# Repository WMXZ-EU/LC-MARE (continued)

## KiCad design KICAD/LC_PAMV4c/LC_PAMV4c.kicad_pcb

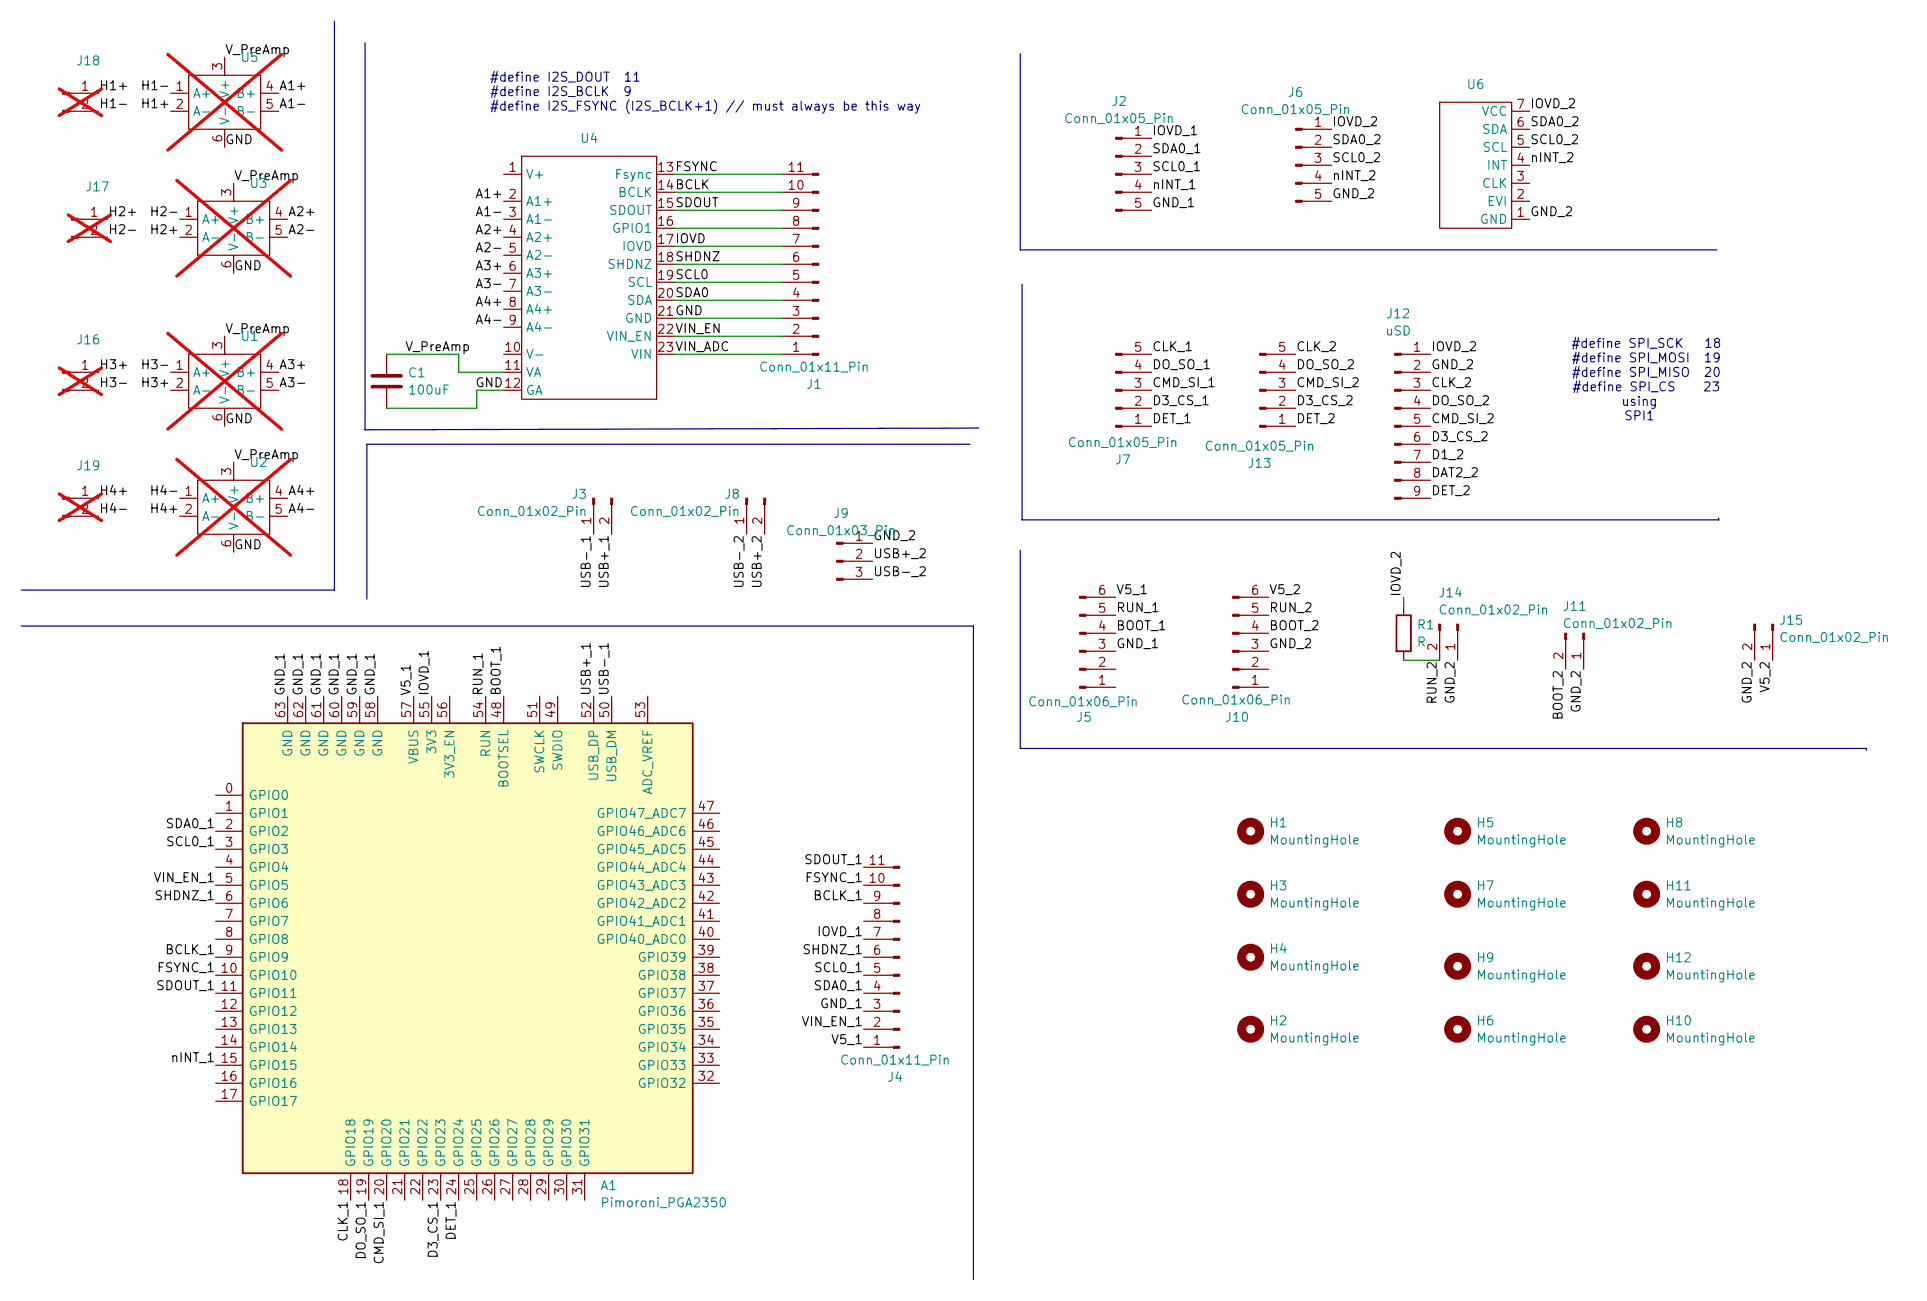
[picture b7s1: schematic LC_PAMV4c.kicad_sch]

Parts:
A1: Pimoroni_PGA2350; pimoroni_pga2350
C1: 100uF; CP_Radial_D4.0mm_P2.00mm
H1, H2, H3, H4, H5, H6, H7, H8, H9, H10, H11, H12: MountingHole; MountingHole_4.3mm_M4
J1, J4: Conn_01x11_Pin; PinHeader_1x11_P2.54mm_Vertical
J2, J6, J7, J13: Conn_01x05_Pin; PinHeader_1x05_P2.54mm_Vertical
J3, J8, J11, J14, J15: Conn_01x02_Pin; PinHeader_1x02_P2.54mm_Vertical
J5, J10: Conn_01x06_Pin; PinHeader_1x06_P2.54mm_Vertical
J9: Conn_01x03_Pin; PinHeader_1x03_P2.54mm_Vertical
J12: uSD
J16, J17, J18, J19: Conn_01x02_Male; Molex_PicoBlade_53048-0210_1x02_P1.25mm_Horizontal; not fitted
R1: R; R_Axial_DIN0204_L3.6mm_D1.6mm_P5.08mm_Horizontal
U1, U2, U3, U5: preAmp2; not fitted
U4: ADC_V2
U6: rtc2

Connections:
/A1+: U4.2 (A1+), U5.4 (B+)
/A1-: U4.3 (A1-), U5.5 (B-)
/A2+: U3.4 (B+), U4.4 (A2+)
/A2-: U3.5 (B-), U4.5 (A2-)
/A3+: U1.4 (B+), U4.6 (A3+)
/A3-: U1.5 (B-), U4.7 (A3-)
/A4+: U2.4 (B+), U4.8 (A4+)
/A4-: U2.5 (B-), U4.9 (A4-)
/BCLK: J1.10, U4.14 (BCLK)
/BCLK_1: A1.9 (GPIO9), J4.9
/BOOT_1: A1.48 (BOOTSEL), J5.4
/BOOT_2: J10.4, J11.2
/CLK_1: A1.18 (GPIO18), J7.5
/CLK_2: J12.3, J13.5
/CMD_SI_1: A1.20 (GPIO20), J7.3
/CMD_SI_2: J12.5, J13.3
/D1_2: J12.7
/D3_CS_1: A1.23 (GPIO23), J7.2
/D3_CS_2: J12.6, J13.2
/DAT2_2: J12.8
/DET_1: A1.24 (GPIO24), J7.1
/DET_2: J12.9, J13.1
/DO_SO_1: A1.19 (GPIO19), J7.4
/DO_SO_2: J12.4, J13.4
/FSYNC: J1.11, U4.13 (Fsync)
/FSYNC_1: A1.10 (GPIO10), J4.10
/GND: C1.2, J1.3, U1.6 (V-), U2.6 (V-), U3.6 (V-), U4.12 (GA), U4.21 (GND), U5.6 (V-)
/GND_1: A1.58 (GND), A1.59 (GND), A1.60 (GND), A1.61 (GND), A1.62 (GND), A1.63 (GND), J2.5, J4.3, J5.3
/GND_2: J6.5, J9.1, J10.3, J11.1, J12.2, J14.1, J15.2, U6.1 (GND)
/H1+: J18.1, U5.2 (A-)
/H1-: J18.2, U5.1 (A+)
/H2+: J17.1, U3.2 (A-)
/H2-: J17.2, U3.1 (A+)
/H3+: J16.1, U1.2 (A-)
/H3-: J16.2, U1.1 (A+)
/H4+: J19.1, U2.2 (A-)
/H4-: J19.2, U2.1 (A+)
/IOVD: J1.7, U4.17 (IOVD)
/IOVD_1: A1.55 (3V3), J2.1, J4.7
/IOVD_2: J6.1, J12.1, R1.1, U6.7 (VCC)
/RUN_1: A1.54 (RUN), J5.5
/RUN_2: J10.5, J14.2, R1.2
/SCL0: J1.5, U4.19 (SCL)
/SCL0_1: A1.3 (GPIO3), J2.3, J4.5
/SCL0_2: J6.3, U6.5 (SCL)
/SDA0: J1.4, U4.20 (SDA)
/SDA0_1: A1.2 (GPIO2), J2.2, J4.4
/SDA0_2: J6.2, U6.6 (SDA)
/SDOUT: J1.9, U4.15 (SDOUT)
/SDOUT_1: A1.11 (GPIO11), J4.11
/SHDNZ: J1.6, U4.18 (SHDNZ)
/SHDNZ_1: A1.6 (GPIO6), J4.6
/USB+_1: A1.52 (USB_DP), J3.2
/USB+_2: J8.2, J9.2
/USB-_1: A1.50 (USB_DM), J3.1
/USB-_2: J8.1, J9.3
/V5_1: A1.57 (VBUS), J4.1, J5.6
/V5_2: J10.6, J15.1
/VIN_ADC: J1.1, U4.23 (VIN)
/VIN_EN: J1.2, U4.22 (VIN_EN)
/VIN_EN_1: A1.5 (GPIO5), J4.2
/V_PreAmp: C1.1, U1.3 (V+), U2.3 (V+), U3.3 (V+), U4.11 (VA), U5.3 (V+)
/nINT_1: A1.15 (GPIO15), J2.4
/nINT_2: J6.4, U6.4 (INT)
unnamed: J1.8, U4.16 (GPIO1)

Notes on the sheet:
#define SPI_SCK 18 #define SPI_MOSI 19 #define SPI_MISO 20 #define SPI_CS 23 using SPI1
#define I2S_DOUT 11 #define I2S_BCLK 9 #define I2S_FSYNC (I2S_BCLK+1) // must always be this way

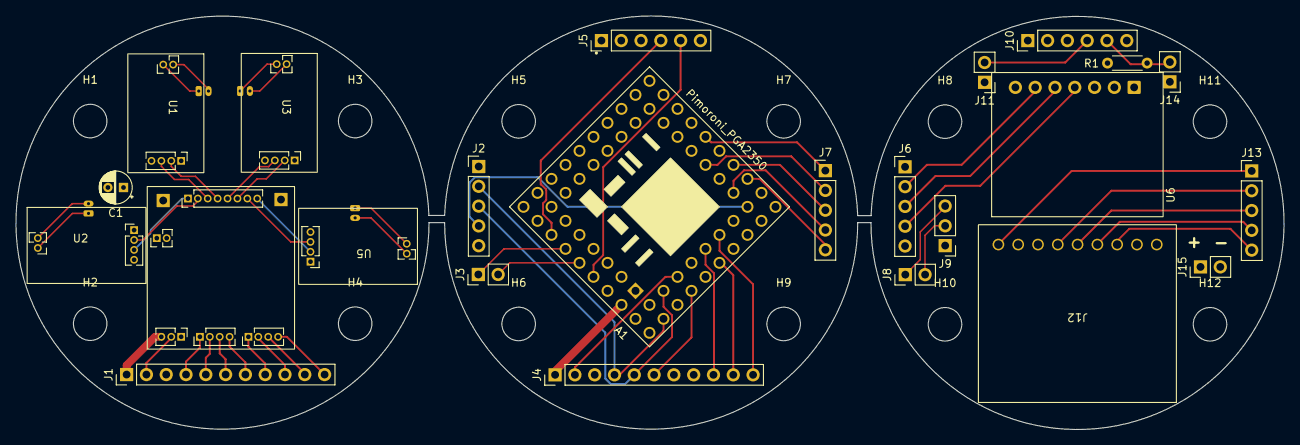
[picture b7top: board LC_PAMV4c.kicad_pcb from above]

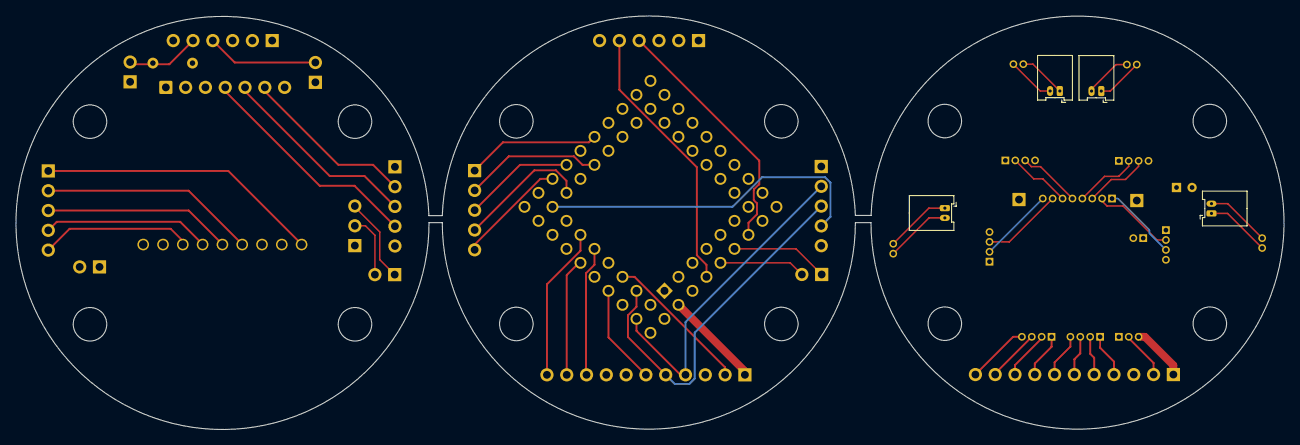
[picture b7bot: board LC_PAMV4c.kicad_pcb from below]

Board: 4 copper layers, 162.7 x 53.1 mm, 40 parts (4 on the bottom side), 63 nets.

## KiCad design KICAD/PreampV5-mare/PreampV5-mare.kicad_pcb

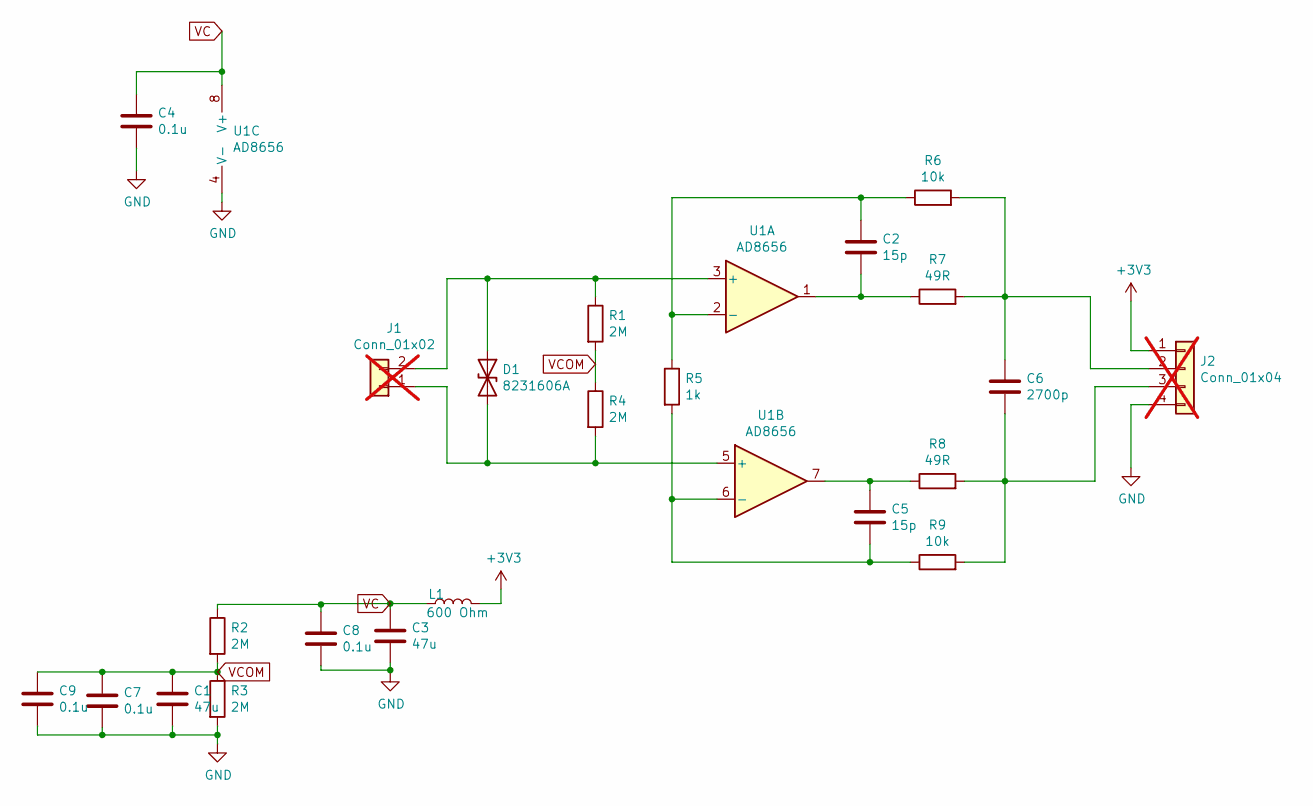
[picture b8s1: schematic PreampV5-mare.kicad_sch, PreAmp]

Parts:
C1, C3: 47u; C_0805_2012Metric
C2, C5: 15p; C_0402_1005Metric
C4, C7, C8, C9: 0.1u; C_0402_1005Metric
C6: 2700p; C_0402_1005Metric
D1: 8231606A; D_0603_1608Metric
J1: Conn_01x02; PinHeader_1x02_P1.27mm_Vertical; not fitted
J2: Conn_01x04; PinHeader_1x04_P1.27mm_Vertical; not fitted
L1: 600 Ohm; L_0603_1608Metric
R1, R2, R3, R4: 2M; R_0402_1005Metric
R5: 1k; R_0402_1005Metric
R6, R9: 10k; R_0402_1005Metric
R7, R8: 49R; R_0402_1005Metric
U1: AD8656; MSOP-8_3x3mm_P0.65mm

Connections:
+3V3: J2.1, L1.2
GND: C1.2, C3.2, C4.2, C7.2, C8.2, C9.2, J2.4, R3.2, U1.4 (V-)
unnamed: C2.2, R7.1, U1.1
unnamed: C5.1, R8.1, U1.7
unnamed: D1.1 (A1), J1.2, R1.1, U1.3 (+)
unnamed: D1.2 (A2), J1.1, R4.2, U1.5 (+)
unnamed: C6.1, J2.2, R6.2, R7.2
unnamed: C6.2, J2.3, R8.2, R9.2
unnamed: C2.1, R5.1, R6.1, U1.2 (-)
unnamed: C5.2, R5.2, R9.1, U1.6 (-)
VC: C3.1, C4.1, C8.1, L1.1, R2.1, U1.8 (V+)
VCOM: C1.1, C7.1, C9.1, R1.2, R2.2, R3.1, R4.1

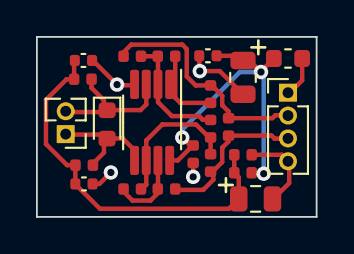
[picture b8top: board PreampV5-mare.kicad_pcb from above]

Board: 2 copper layers, 15.5 x 10.0 mm, 23 parts (0 on the bottom side), 12 nets.

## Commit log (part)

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2024-07-26 initial upload
2024-07-30 modified menu
2024-07-30 corrected installation
2024-07-31 microPAM_GUI
2024-08-02 adapted adc to 2ß24 hw
2024-08-04 changed reference day
2024-08-05 changed mgetEntry to msendEntry
2024-08-07 07-08-24
2024-08-19 update baseboard
2024-08-22 V22-08-24
2024-09-19 added pream-FET
2024-09-27 updated for fet-preamp
2024-10-09 V09-10-24
2024-12-19 v19-12-24
2025-02-03 v03-02-25
2025-02-05 v05-02-25
2025-02-07 added LC_PAM_sp.step
2025-02-26 V26-02
2025-07-23 V23-07-25
2025-07-23 uploaded pdfs
2025-07-23 removed lock
2025-08-08 added adalogger_v2
2025-10-07 v07-10-25
2025-10-07 binary 07-10-25
2025-10-17 V17-10-25
2025-10-17 update firmware
2025-10-18 18-10-25
2025-11-21 Nov update
2025-12-06 remove local neo-pixel
2025-12-23 LC_PAM4b2
2025-12-24 24-12-25
2025-12-24 24.12
2025-12-27 v27-12-25
2025-12-30 30-12-2025
2025-12-30 remove .idea
2025-12-30 corrected wav header
2025-12-30 corrected insertChunk
2026-01-03 v3-1-26
2026-01-03 added LC-mare file utility
2026-01-10 V10-jan-26
2026-01-10 Removed development files
2026-01-10 removed LC_ADC
2026-01-12 v12.01.26
2026-01-25 V2.0.3
2026-02-01 v01-02-26
2026-02-05 05-02-2026
2026-02-05 Added hourly record periods
2026-02-05 corrected header info
2026-02-05 V05-02.2026
2026-02-09 Update Assembly
2026-03-09 09-03-26
2026-03-09 09-03-26-2
2026-03-15 15-03-26
2026-03-24 V24-03-2026
2026-03-25 v25-03-26
2026-03-28 added ecs poster
2026-04-07 V07-04-2026
2026-04-11 V11-04-26
2026-04-12 12-04-26
2026-04-18 V18-04-26
2026-05-05 V05-05-2026
2026-05-07 updated Queue to combine data to larger block
2026-05-08 first running version on rp2350 with psram
2026-05-08 compiled version
2026-05-08 updated viewer
2026-05-09 clean-up
2026-05-09 switch between rp2040 and rp2350
2026-05-09 updated microPAM.py
2026-05-09 recompiled
2026-05-10 clean-up buffer size definitions
2026-05-10 corrected wav file queueing
2026-05-10 update viewer
2026-05-11 add hall sensor
2026-05-14 miner changes
2026-05-14 updated GUI
2026-05-17 created RTC-RV3028
2026-05-19 V19-05-26
2026-05-19 Add LC_PAM4b2b
2026-05-19 removed outdated pictures
2026-05-19 minor code clean-up
2026-05-23 corrected hibernate
2026-05-24 Added python utilities
2026-05-24 wav file meta data corrected
2026-05-24 recompiled version 24-05-26
2026-05-24 wav file metadata corrected
2026-05-24 removed .idea
2026-05-26 corrected meta information processing
2026-05-27 mods to UI
2026-06-01 KICAD new components
2026-06-07 Modified startup procedure
2026-06-08 renaming files
2026-06-09 corrected queueing
2026-06-09 modified start-up logic
2026-06-12 clean-up LC_Mare
2026-06-12 rename readme file
2026-06-13 corrected filing.cxx
2026-06-13 corrected Queue.cxx
2026-06-16 initial upload microPAM_V4
2026-06-17 minor change
2026-06-17 drill file
2026-06-21 V21-06
2026-06-21 corrected process.cxx
2026-06-22 moved memcpy from process to acq_isr
2026-06-22 epdate hex file
2026-06-23 replaced Serial-printf bysequences of Serial.print
2026-06-23 rewrote print(,HEX)
2026-06-23 working? version for 1.61
2026-06-23 use logBuffer for printout
2026-06-23 uodate readme
2026-06-25 started detection function
2026-06-25 added copyright notice
2026-06-25 generated utils.cxx
2026-06-25 added builds
2026-06-26 added classifier
2026-06-26 version 4.1.0
2026-06-26 Added GUI to control parameter input
2026-06-27 adapted LC_Mare to microPAM_V4
2026-06-27 compiled rp-boards
2026-06-28 firmware 4.2.0
2026-06-28 compiled tools
